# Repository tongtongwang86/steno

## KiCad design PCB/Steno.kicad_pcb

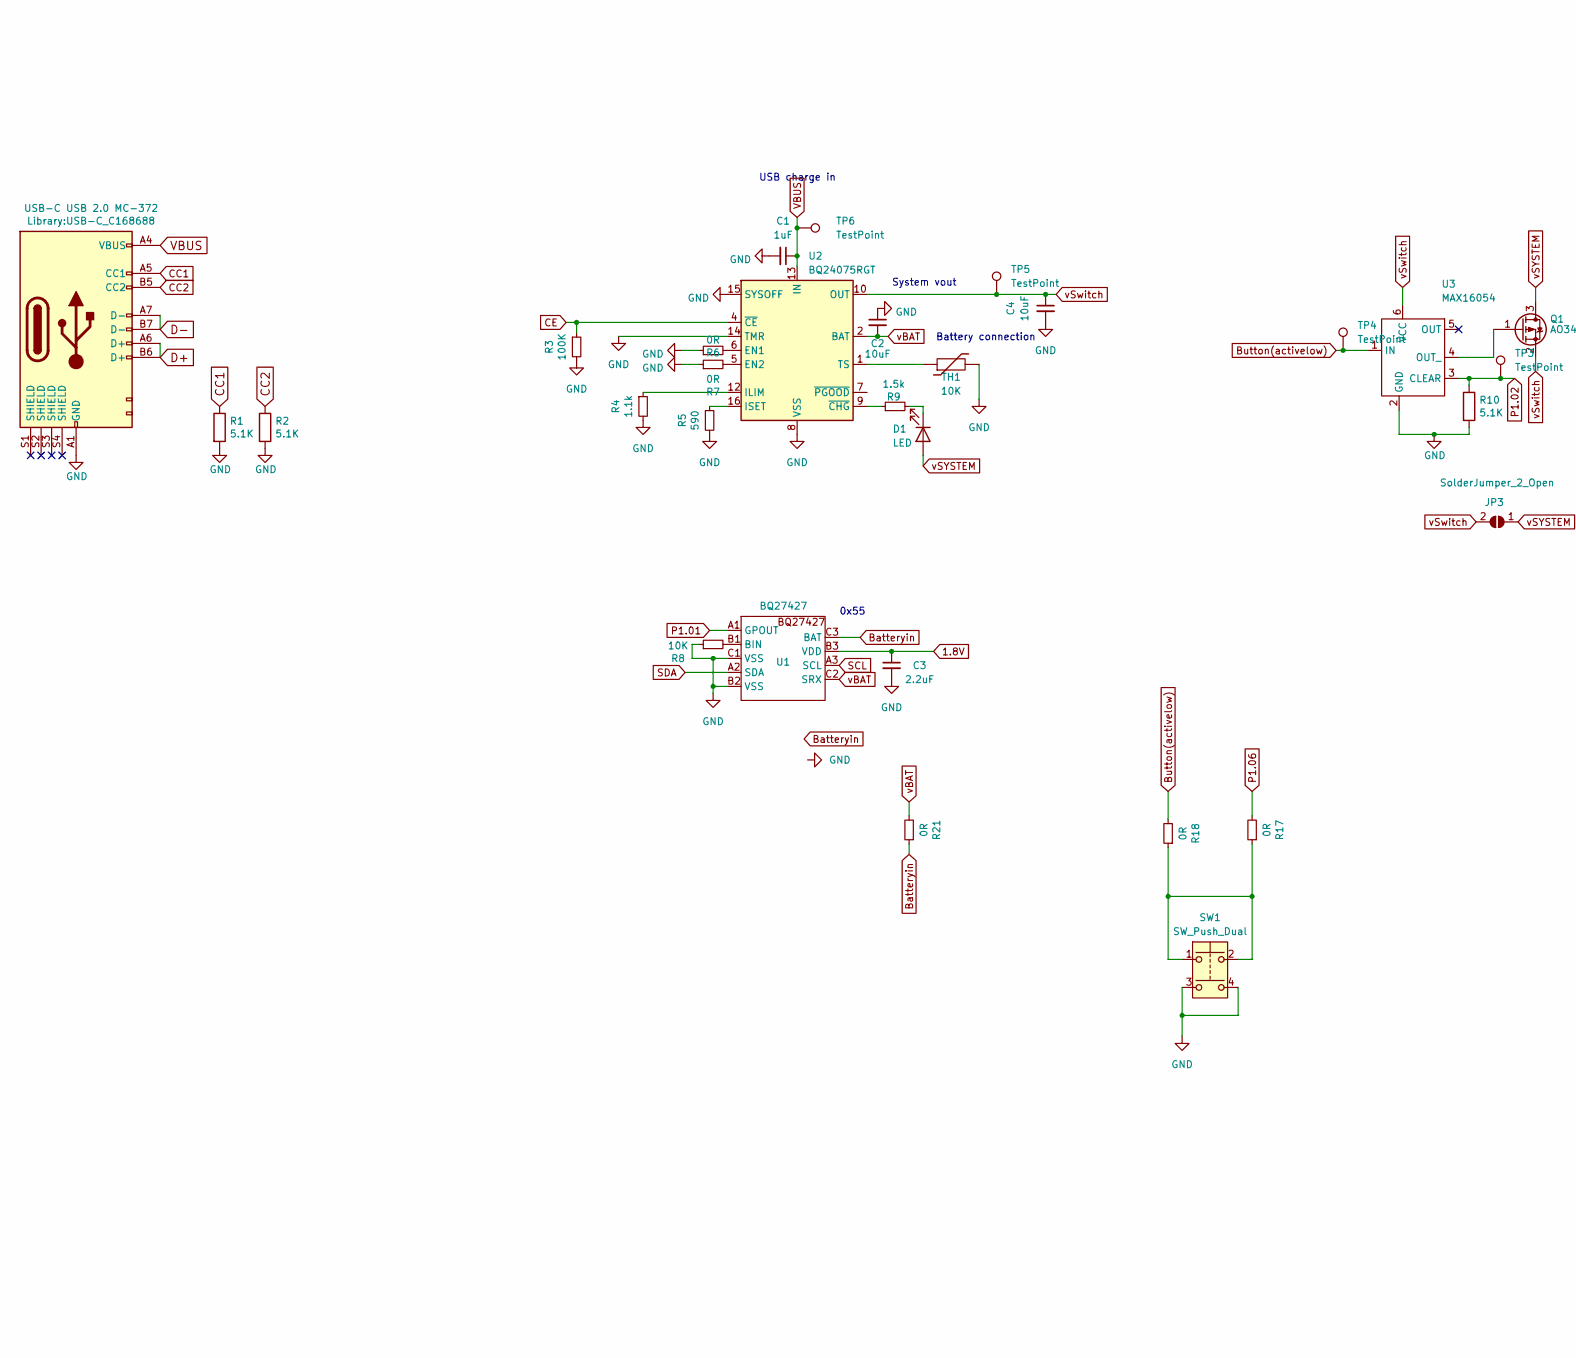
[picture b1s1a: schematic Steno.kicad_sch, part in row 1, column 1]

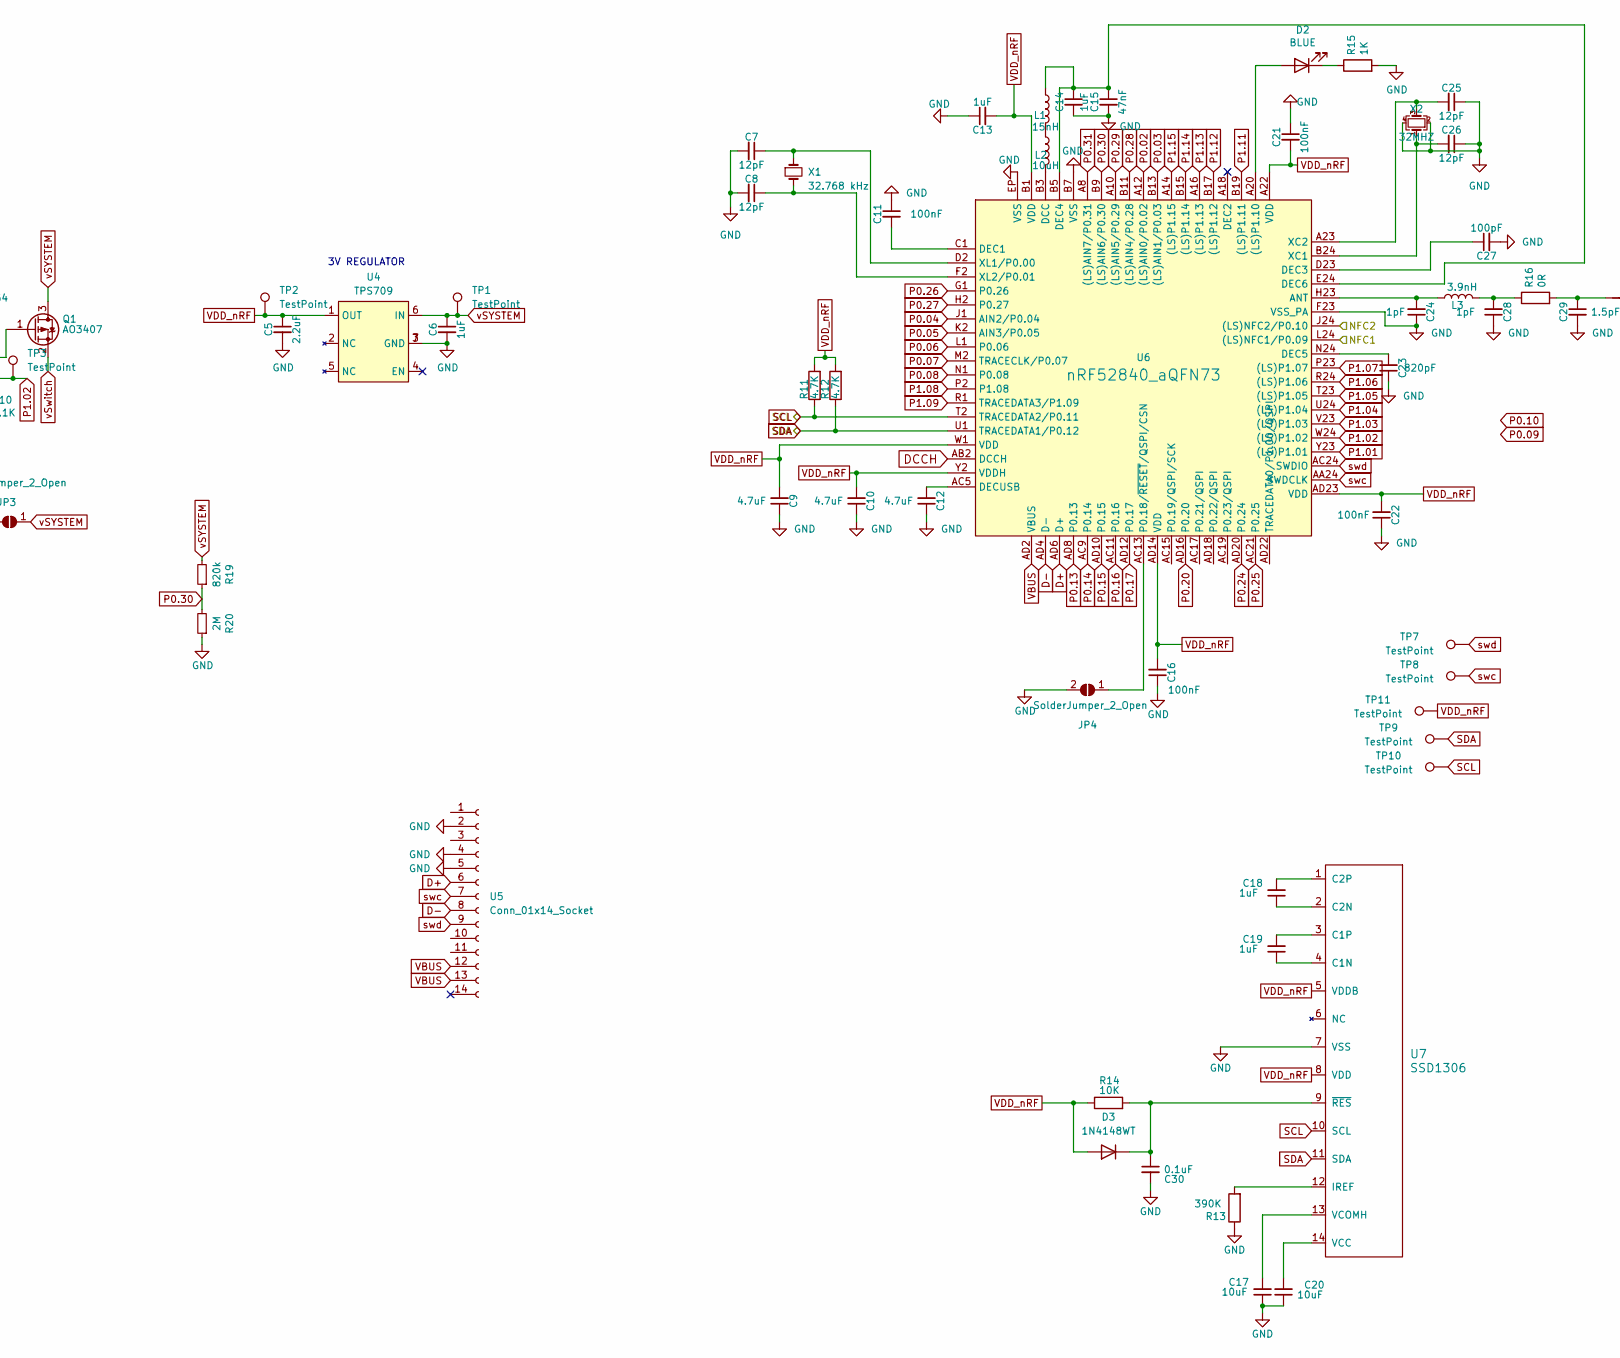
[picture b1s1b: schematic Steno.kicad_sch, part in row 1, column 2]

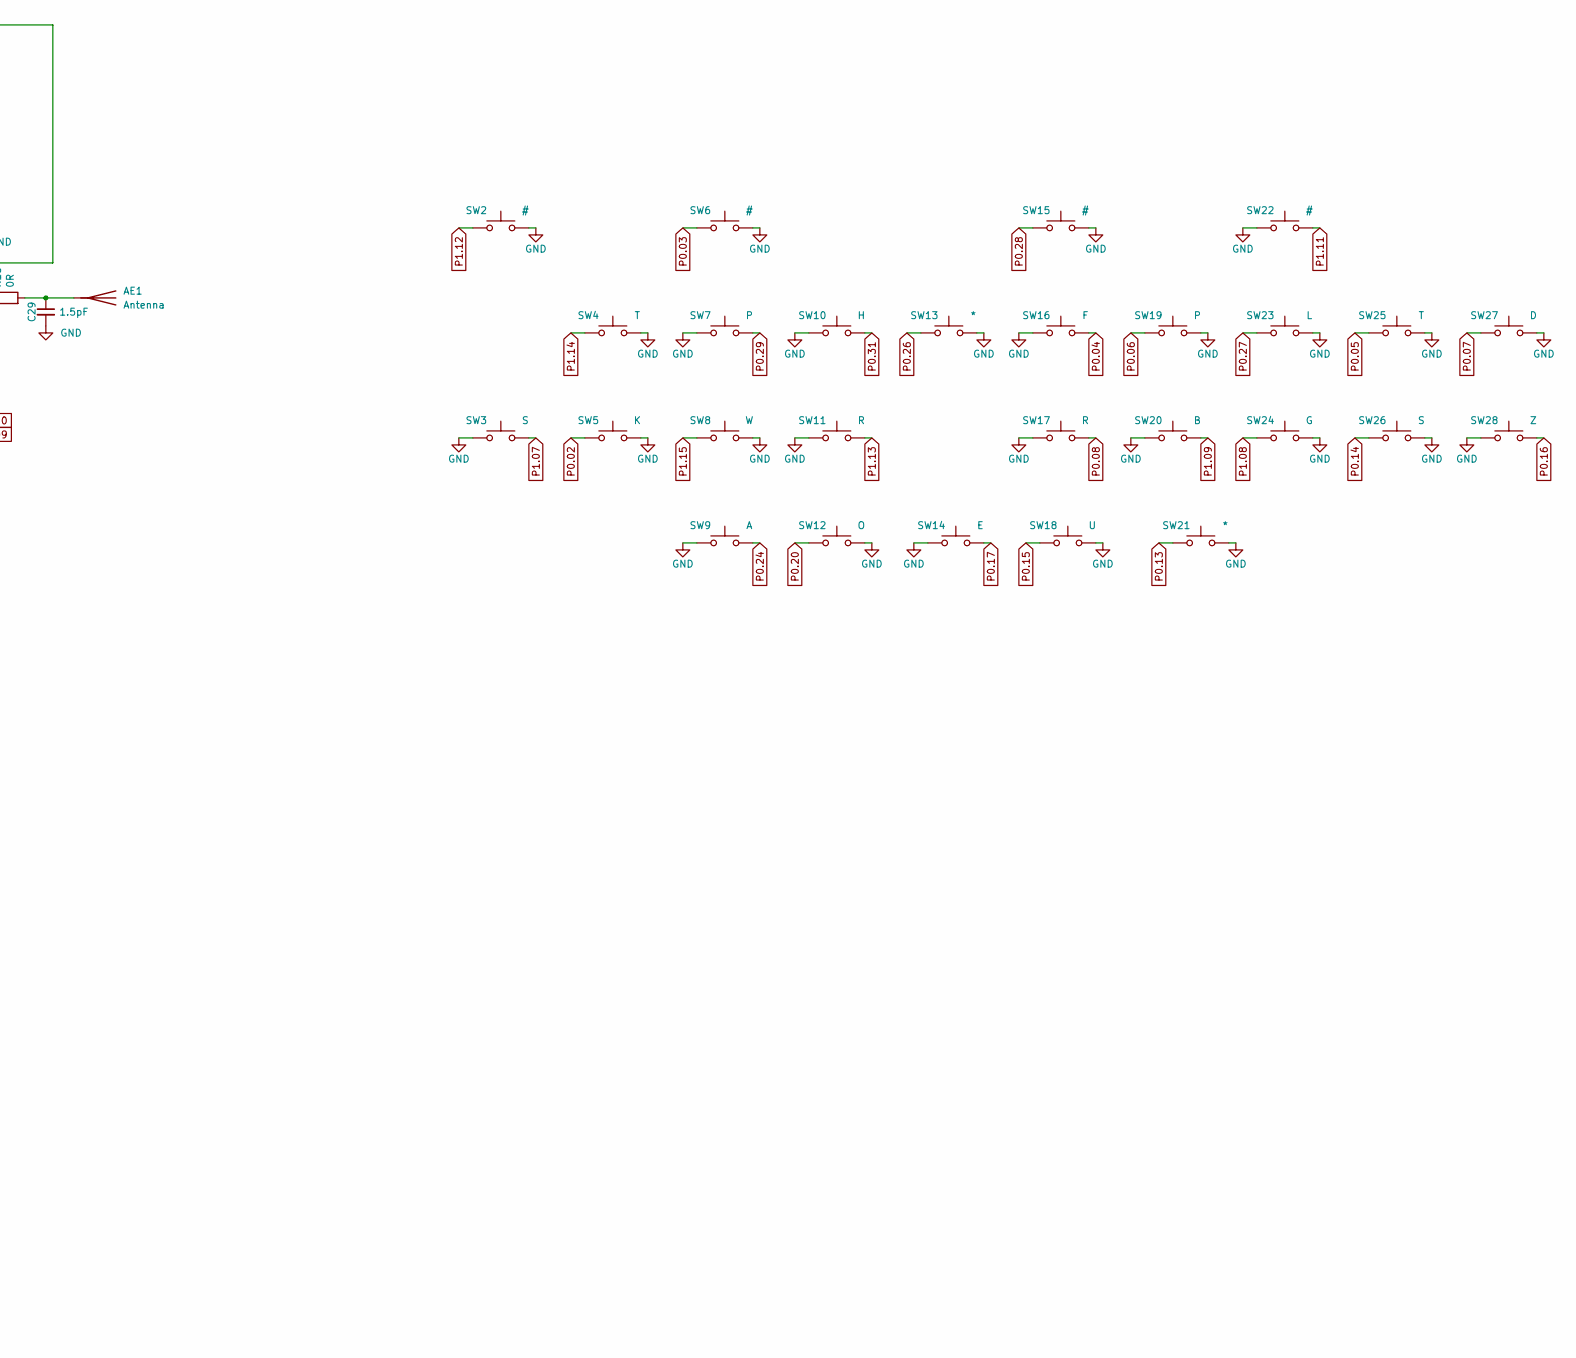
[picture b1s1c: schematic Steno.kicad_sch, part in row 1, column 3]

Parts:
AE1: Antenna; 2.4GHz-meander-antenna-v2
C1, C6: 1uF; 0402
C2, C4, C17, C20: 10uF; 0402
C3, C5: 2.2uF; 0402
C7, C8, C25, C26: 12pF; C_0402_1005Metric
C9, C10, C12: 4.7uF; C_0402_1005Metric
C11, C16, C21, C22: 100nF; C_0402_1005Metric
C13, C14, C18, C19: 1uF; C_0402_1005Metric
C15: 47nF; C_0402_1005Metric
C23: 820pF; C_0402_1005Metric
C24, C28: 1pF; C_0402_1005Metric
C27: 100pF; C_0402_1005Metric
C29: 1.5pF; C_0402_1005Metric
C30: 0.1uF; C_0402_1005Metric
D1: LED; 0402
D2: BLUE; LED_0402_1005Metric
D3: 1N4148WT; D_SOD-523
J1: USB-C USB 2.0 MC-372; USB-C_C168688
JP3, JP4: SolderJumper_2_Open; SolderJumper-2_P1.3mm_Open_TrianglePad1.0x1.5mm
L1: 15nH; L_0402_1005Metric
L2: 10uH; L_0402_1005Metric
L3: 3.9nH; L_0402_1005Metric
Q1: AO3407; SOT-23
R1, R2, R10: 5.1K; R_0402_1005Metric
R3: 100K; 0402
R4: 1.1k; 0402
R5: 590; 0402
R6, R7, R16, R17, R18, R21: 0R; 0402
R8, R14: 10K; 0402
R9: 1.5k; 0402
R11, R12: 4.7K; R_0402_1005Metric
R13: 390K; R_0402_1005Metric
R15: 1K; R_0402_1005Metric
R19: 820k; 0402
R20: 2M; 0402
SW1: SW_Push_Dual; 5x5button
SW2, SW6, SW15, SW22: #; CustomHotswap
SW3, SW26: S; CustomHotswap
SW4, SW25: T; CustomHotswap
SW5: K; CustomHotswap
SW7, SW19: P; CustomHotswap
SW8: W; CustomHotswap
SW9: A; CustomHotswap
SW10: H; CustomHotswap
SW11, SW17: R; CustomHotswap
SW12: O; CustomHotswap
SW13, SW21: *; CustomHotswap
SW14: E; CustomHotswap
SW16: F; CustomHotswap
SW18: U; CustomHotswap
SW20: B; CustomHotswap
SW23: L; CustomHotswap
SW24: G; CustomHotswap
SW27: D; CustomHotswap
SW28: Z; CustomHotswap
TH1: 10K; 0402
TP1, TP2, TP3, TP4, TP5, TP6, TP7, TP8, TP9, TP10, TP11: TestPoint; testPads
U1: BQ27427; Texas_DSBGA-9_1.62mmx1.58mm_Layout3x3_P0.5mm
U2: BQ24075RGT; VQFN-16-1EP_3x3mm_P0.5mm_EP1.6x1.6mm
U3: MAX16054; SOT-23-6
U4: TPS709; DRV 6PIN
U5: Conn_01x14_Socket; FPC
U6: nRF52840_aQFN73; AQFN-73-1EP_7x7mm_P0.5mm_NRF52840-custom
U7: SSD1306; SSD1306_OLED-0.91-128x32
X1: 32.768 kHz; Crystal_SMD_2012-2Pin_2.0x1.2mm; Manufacturer Part SC20S-12.5PF20PPM; LCSC Part C97607
X2: 32MHZ; crystal 32mhz

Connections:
1.8V: C3.1, U1.B3 (VDD)
/NFC1: U6.L24 ((LS)NFC1/P0.09)
/NFC2: U6.J24 ((LS)NFC2/P0.10)
Batteryin: R21.1, U1.C3 (BAT)
Button(activelow): R18.2, TP4.1, U3.1 (IN)
CC1: J1.A5 (CC1), R1.1
CC2: J1.B5 (CC2), R2.1
CE: R3.1, U2.4 (~CE)
D+: J1.A6 (D+), J1.B6 (D+), U5.6, U6.AD6 (D+)
D-: J1.A7 (D-), J1.B7 (D-), U5.8, U6.AD4 (D-)
DCCH: U6.AB2 (DCCH)
GND: C1.2, C2.1, C3.2, C4.2, C5.2, C6.2, C7.2, C8.2, C9.1, C10.1, C11.1, C12.1, C13.1, C14.2, C15.2, C16.1, C17.1, C20.1, C21.1, C22.1, C23.1, C24.1, C25.1, C26.1, C27.2, C28.1, C29.2, C30.2, J1.A1 (GND), JP4.2 (B), R1.2, R2.2, R3.2, R4.2, R5.2, R6.1, R7.1, R8.1, R10.2, R13.1, R15.2, R20.1, SW1.3, SW1.4, SW2.2, SW3.1, SW4.2, SW5.2, SW6.2, SW7.1, SW8.2, SW9.1, SW10.1, SW11.1, SW12.2, SW13.2, SW14.1, SW15.2, SW16.1, SW17.1, SW18.2, SW19.2, SW20.1, SW21.2, SW22.1, SW23.2, SW24.2, SW25.2, SW26.2, SW27.2, SW28.1, TH1.2, U1.B2 (VSS), U1.C1 (VSS), U2.8 (VSS), U2.14 (TMR), U2.15 (SYSOFF), U2.17 (VSS), U3.2 (GND), U4.3 (GND), U4.7 (GND), U5.2, U5.4, U5.5, U6.B7 (VSS), U6.EP (VSS), U6.F23 (VSS_PA), U7.7 (VSS), X2.2, X2.4
unnamed: AE1.1 (A), C29.1, R16.2
unnamed: C28.2, L3.2, R16.1
unnamed: D1.1 (K), R9.2
unnamed: D2.2 (A), U6.A20 ((LS)P1.10)
unnamed: D2.1 (K), R15.1
unnamed: C30.1, D3.1 (K), R14.2, U7.9 (~RES)
unnamed: JP4.1 (A), U6.AC13 (P0.18/~RESET/QSPI/CSN)
unnamed: L1.2, L2.1
unnamed: Q1.1 (G), U3.4 (OUT_)
unnamed: R17.1, R18.1, SW1.1, SW1.2
unnamed: R8.2, U1.B1 (BIN)
unnamed: R6.2, U2.6 (EN1)
unnamed: R7.2, U2.5 (EN2)
unnamed: R4.1, U2.12 (ILIM)
unnamed: R5.1, U2.16 (ISET)
unnamed: TH1.1, U2.1 (TS)
unnamed: R9.1, U2.9 (~CHG)
unnamed: C24.2, L3.1, U6.H23 (ANT)
unnamed: L2.2, U6.B3 (DCC)
unnamed: C11.2, U6.C1 (DEC1)
unnamed: C27.1, U6.D23 (DEC3)
unnamed: C14.1, C15.1, L1.1, U6.B5 (DEC4), U6.E24 (DEC6)
unnamed: C23.2, U6.N24 (DEC5)
unnamed: C12.2, U6.AC5 (DECUSB)
unnamed: C26.2, U6.B24 (XC1), X2.1
unnamed: C25.2, U6.A23 (XC2), X2.3
unnamed: C7.1, U6.D2 (XL1/P0.00), X1.1
unnamed: C8.1, U6.F2 (XL2/P0.01), X1.2
unnamed: C19.1, U7.4 (C1N)
unnamed: C19.2, U7.3 (C1P)
unnamed: C18.1, U7.2 (C2N)
unnamed: C18.2, U7.1 (C2P)
unnamed: R13.2, U7.12 (IREF)
unnamed: C20.2, U7.14 (VCC)
unnamed: C17.2, U7.13 (VCOMH)
P0.02: SW5.1, U6.A12 ((LS)AIN0/P0.02)
P0.03: SW6.1, U6.B13 ((LS)AIN1/P0.03)
P0.04: SW16.2, U6.J1 (AIN2/P0.04)
P0.05: SW25.1, U6.K2 (AIN3/P0.05)
P0.06: SW19.1, U6.L1 (P0.06)
P0.07: SW27.1, U6.M2 (TRACECLK/P0.07)
P0.08: SW17.2, U6.N1 (P0.08)
P0.13: SW21.1, U6.AD8 (P0.13)
P0.14: SW26.1, U6.AC9 (P0.14)
P0.15: SW18.1, U6.AD10 (P0.15)
P0.16: SW28.2, U6.AC11 (P0.16)
P0.17: SW14.2, U6.AD12 (P0.17)
P0.20: SW12.1, U6.AD16 (P0.20)
P0.24: SW9.2, U6.AD20 (P0.24)
P0.25: U6.AC21 (P0.25)
P0.26: SW13.1, U6.G1 (P0.26)
P0.27: SW23.1, U6.H2 (P0.27)
P0.28: SW15.1, U6.B11 ((LS)AIN4/P0.28)
P0.29: SW7.2, U6.A10 ((LS)AIN5/P0.29)
P0.30: R19.1, R20.2, U6.B9 ((LS)AIN6/P0.30)
P0.31: SW10.2, U6.A8 ((LS)AIN7/P0.31)
P1.01: U1.A1 (GPOUT), U6.Y23 ((LS)P1.01)
P1.02: R10.1, TP3.1, U3.3 (CLEAR), U6.W24 ((LS)P1.02)
P1.03: U6.V23 ((LS)P1.03)
P1.04: U6.U24 ((LS)P1.04)
P1.05: U6.T23 ((LS)P1.05)
P1.06: R17.2, U6.R24 ((LS)P1.06)
P1.07: SW3.2, U6.P23 ((LS)P1.07)
P1.08: SW24.1, U6.P2 (P1.08)
P1.09: SW20.2, U6.R1 (TRACEDATA3/P1.09)
P1.11: SW22.2, U6.B19 ((LS)P1.11)
P1.12: SW2.1, U6.B17 ((LS)P1.12)
P1.13: SW11.2, U6.A16 ((LS)P1.13)
P1.14: SW4.1, U6.B15 ((LS)P1.14)
P1.15: SW8.1, U6.A14 ((LS)P1.15)
SCL: R11.1, TP10.1, U1.A3 (SCL), U6.T2 (TRACEDATA2/P0.11), U7.10 (SCL)
SDA: R12.1, TP9.1, U1.A2 (SDA), U6.U1 (TRACEDATA1/P0.12), U7.11 (SDA)
VBUS: C1.1, J1.A4 (VBUS), TP6.1, U2.13 (IN), U5.12, U5.13, U6.AD2 (VBUS)
VDD_nRF: C5.1, C9.2, C10.2, C13.2, C16.2, C21.2, C22.2, D3.2 (A), R11.2, R12.2, R14.1, TP2.1, TP11.1, U4.1 (OUT), U6.A22 (VDD), U6.AD14 (VDD), U6.AD23 (VDD), U6.B1 (VDD), U6.W1 (VDD), U6.Y2 (VDDH), U7.5 (VDDB), U7.8 (VDD)
swc: TP8.1, U5.7, U6.AA24 (SWDCLK)
swd: TP7.1, U5.9, U6.AC24 (SWDIO)
vBAT: C2.2, R21.2, U1.C2 (SRX), U2.2 (BAT), U2.3 (BAT)
vSYSTEM: C6.1, D1.2 (A), JP3.1 (A), Q1.3 (D), R19.2, TP1.1, U4.6 (IN)
vSwitch: C4.1, JP3.2 (B), Q1.2 (S), TP5.1, U2.10 (OUT), U2.11 (OUT), U3.6 (VCC)

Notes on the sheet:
USB charge in
System vout
3V REGULATOR
0x55
Battery connection

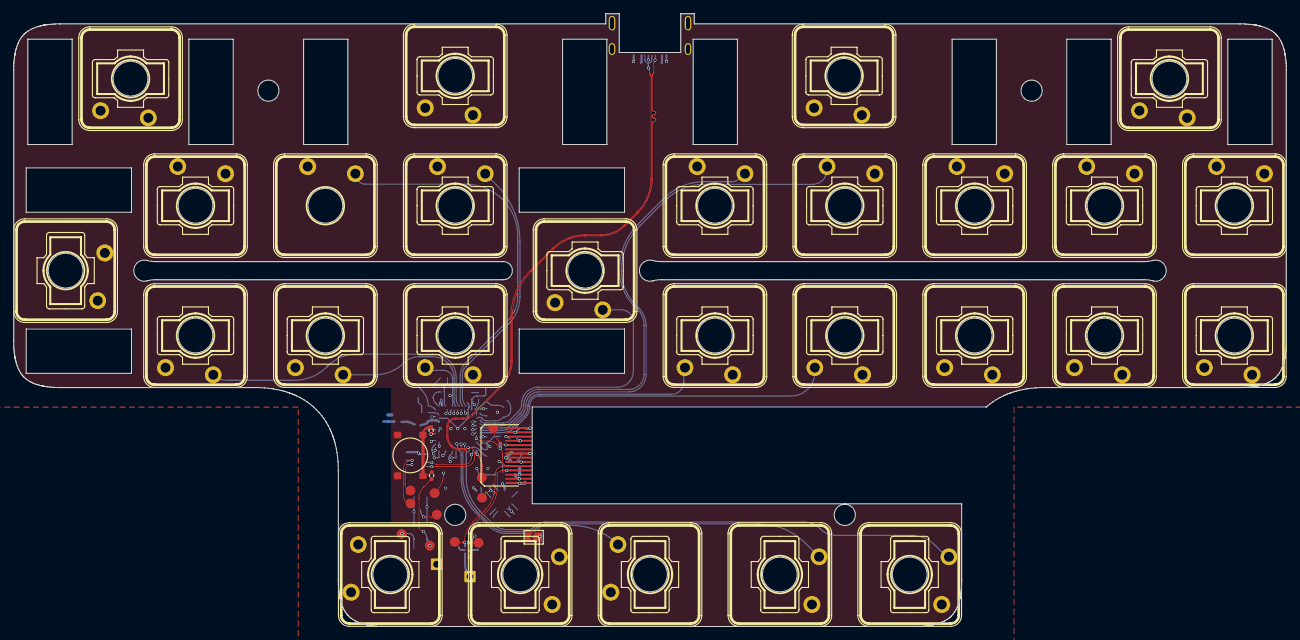
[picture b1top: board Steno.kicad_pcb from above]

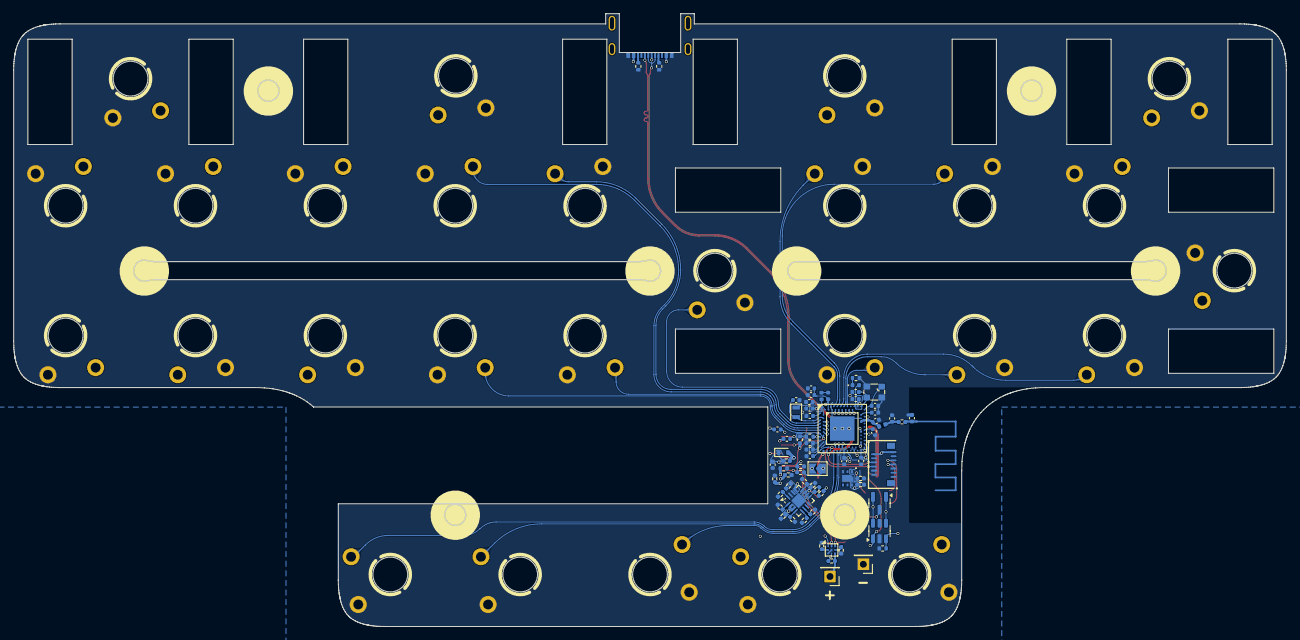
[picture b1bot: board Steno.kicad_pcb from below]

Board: 4 copper layers, 186.7 x 89.9 mm, 111 parts (69 on the bottom side), 84 nets.

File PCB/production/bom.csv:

Designator,Footprint,Quantity,Value,LCSC Part #
"C1, C13, C14, C18, C19, C6",0402,6,1uF,
"C10, C12, C9",0402,3,4.7uF,
"C11, C16, C21, C22",0402,4,100nF,
C15,0402,1,47nF,
"C17, C2, C20, C4",0402,4,10uF,
C23,0402,1,820pF,
"C24, C28",0402,2,1pF,
"C25, C26, C7, C8",0402,4,12pF,
C27,0402,1,100pF,
C29,0402,1,1.5pF,
"C3, C5",0402,2,2.2uF,
C30,0402,1,0.1uF,
D1,0402,1,LED,
D2,0402,1,BLUE,
D3,D_SOD-523,1,1N4148WT,
J1,USB-C_C168688,1,USB-C USB 2.0 MC-372,
"JP3, JP4",SolderJumper-2_P1.3mm_Open_TrianglePad1.0x1.5mm,2,SolderJumper_2_Open,
L1,0402,1,15nH,
L2,0402,1,10uH,
L3,0402,1,3.9nH,
Q1,SOT-23,1,AO3407,
"R1, R10, R2",0402,3,5.1K,
"R11, R12",0402,2,4.7K,
R13,0402,1,390K,
"R14, R8, TH1",0402,3,10K,
R15,0402,1,1K,
"R16, R17, R18, R21, R6, R7",0402,6,0R,
R19,0402,1,820k,
R20,0402,1,2M,
R3,0402,1,100K,
R4,0402,1,1.1k,
R5,0402,1,590,
R9,0402,1,1.5k,
SW1,5x5button,1,SW_Push_Dual,
U1,Texas_DSBGA-9_1.62mmx1.58mm_Layout3x3_P0.5mm,1,BQ27427,
U2,VQFN-16-1EP_3x3mm_P0.5mm_EP1.6x1.6mm,1,BQ24075RGT,
U3,SOT-23-6,1,MAX16054,
U4,DRV 6PIN,1,TPS709,
U5,FPC,1,Conn_01x14_Socket,
U6,AQFN-73-1EP_7x7mm_P0.5mm_NRF52840-custom,1,nRF52840_aQFN73,
U7,SSD1306_OLED-0.91-128x32,1,SSD1306,
X1,Crystal_SMD_2012-2Pin_2.0x1.2mm,1,32.768 kHz,C97607
X2,crystal 32mhz,1,32MHZ,

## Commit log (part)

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2025-06-07 init
2025-06-07 new board
2025-06-07 output hex
2025-06-07 new ci
2025-06-07 changed ci
2025-06-07 new keymap
2025-06-07 fuel gauge
2025-06-07 added pincontrol for i2c0
2025-06-07 new steno keymap
2025-06-07 keymap
2025-06-07 nkro
2025-06-07 nkro2
2025-06-07 nkro3
2025-06-07 display and bluetooth
2025-06-07 fix keymap
2025-06-07 i2c oled
2025-06-07 oled
2025-06-07 keymap2
2025-06-07 fixed i2c pins
2025-06-07 update display
2025-06-07 display
2025-06-07 display3
2025-06-07 display4
2025-06-07 display5
2025-06-07 display6
2025-06-07 fast i2c
2025-06-07 dedicated ui thread
2025-06-08 128x32
2025-06-08 edited kconfig
2025-06-08 kconfig2
2025-06-08 kconfig3
2025-06-08 kconfig
2025-06-08 kconfig again
2025-06-08 dts2
2025-06-08 dts3
2025-06-08 dts4
2025-06-08 dts5
2025-06-13 128x64
2025-06-13 switch i2c pins
2025-06-13 disabled fuel gauge to test display
2025-06-13 invert horizontal and vertical
2025-06-13 invert horizontally
2025-06-24 added pcb
2025-06-24 momentary layer
2025-06-24 ds store
2025-06-30 new keymap for new pcb
2025-06-30 voltage divider for battery
2025-06-30 show battery percentage
2025-06-30 fuel gauge calibration
2025-07-06 try fuel gauge again
2025-07-06 fix build error
